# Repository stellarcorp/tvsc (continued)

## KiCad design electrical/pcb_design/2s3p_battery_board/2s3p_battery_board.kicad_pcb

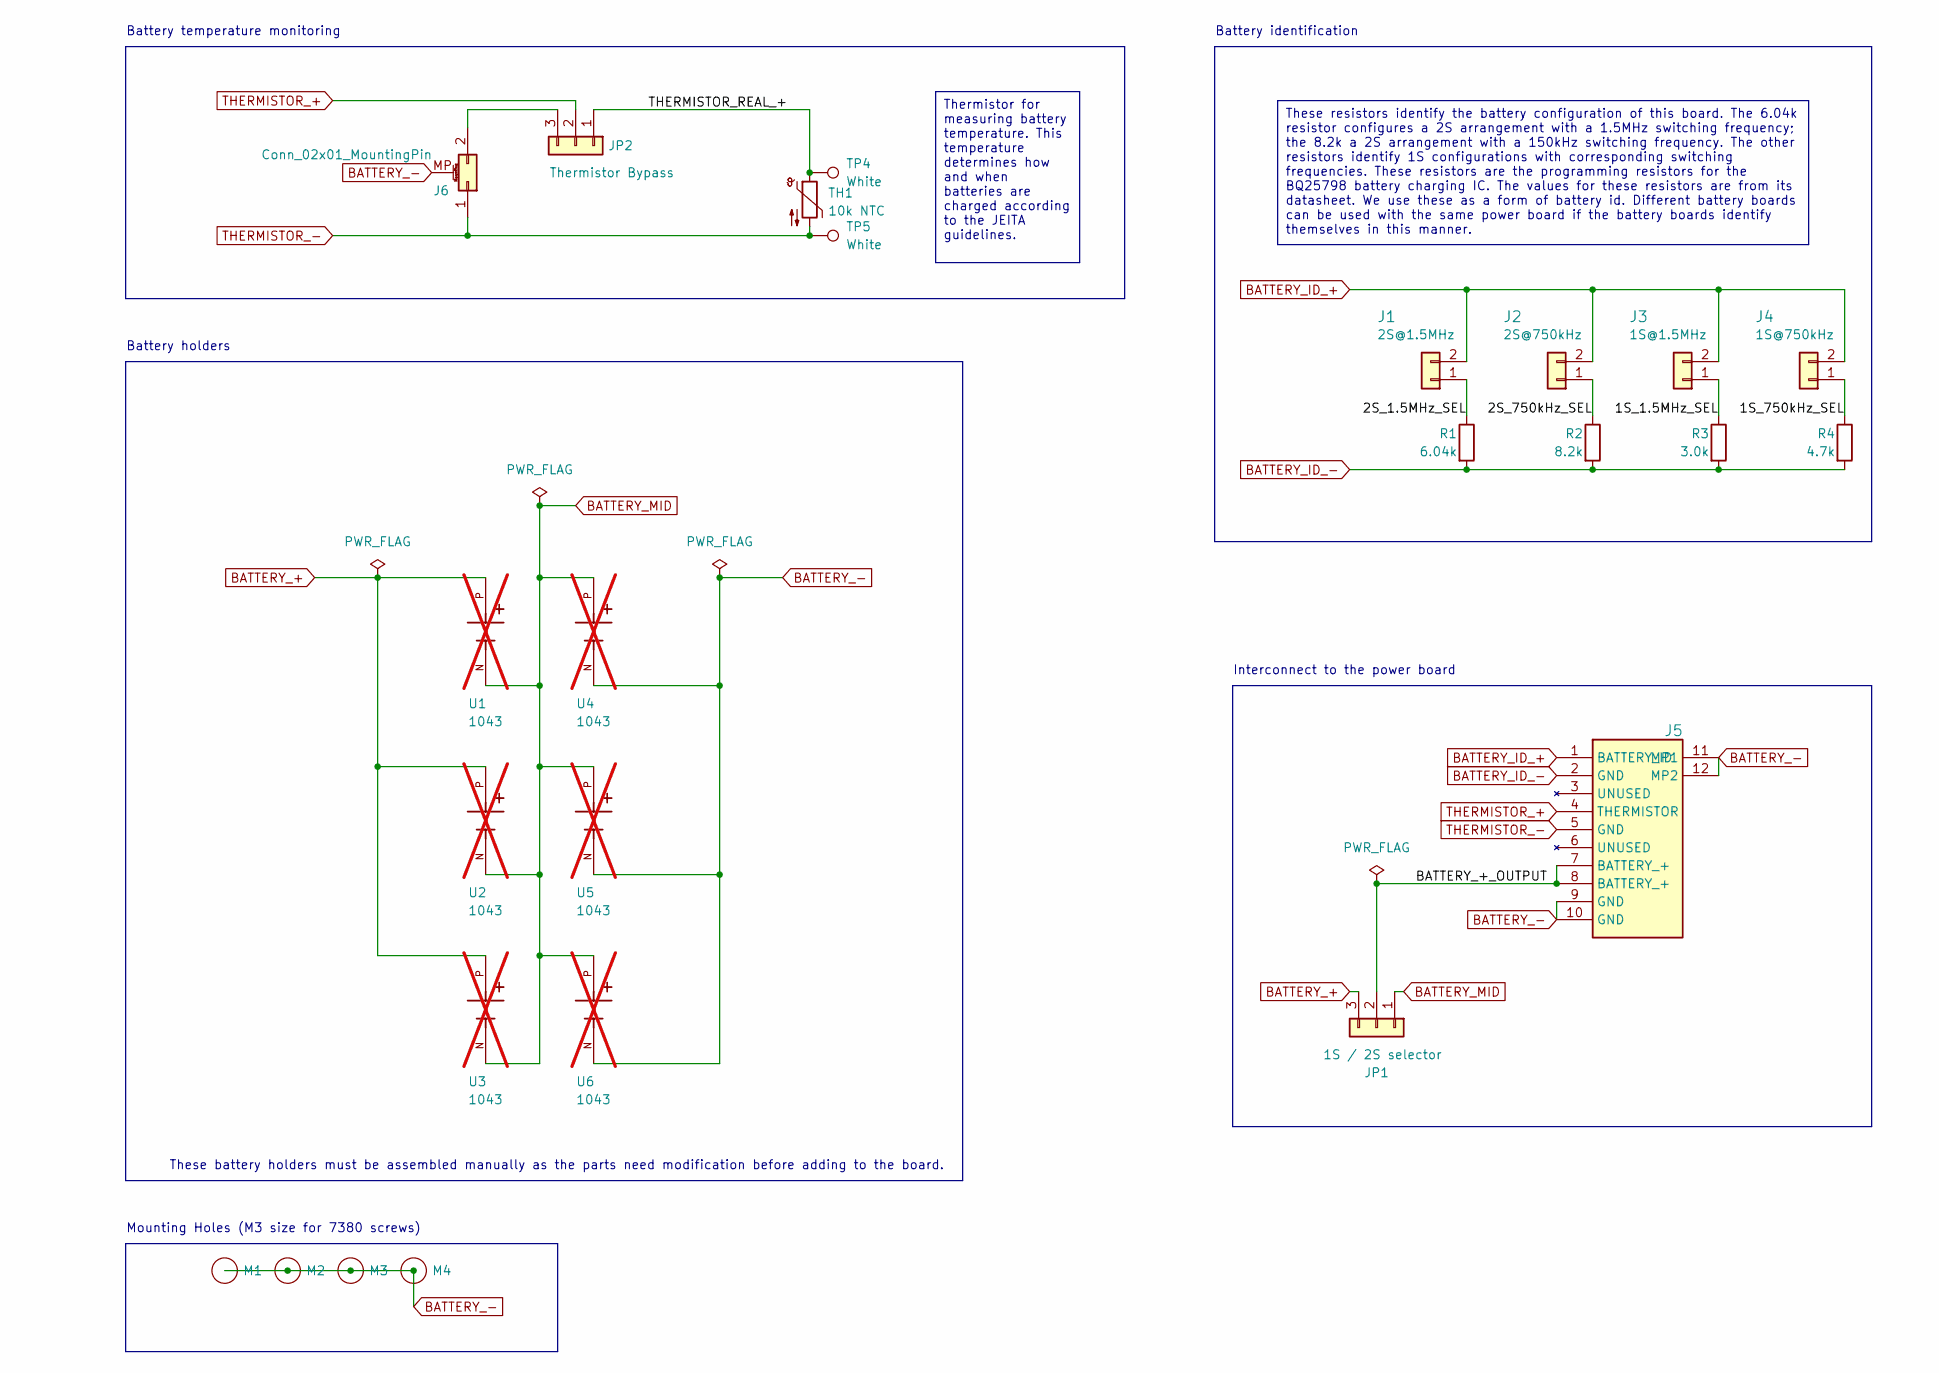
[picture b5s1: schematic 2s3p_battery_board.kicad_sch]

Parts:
J1, J2, J3, J4: 2-pin Header; PinHeader_1x02_P1.27mm_Vertical; Manufacturer Part Number X1321WV-2x01J-C30D23
J5: Interconnect_Battery_Power-Battery_side; 504050-1091; MPN C5375652
J6: Conn_02x01_MountingPin; Molex_Pico-Clasp_501331-0207_1x02-1MP_P1.00mm_Vertical; MPN C587859
JP1, JP2: Conn_01x03; HDRV3W64P0X254_1X3_762X254X869P; MPN C2915006; Mouser Part Number 710-61300311121
M1, M2, M3, M4: MountingHole_3.2mm_M3_ISO7380_Pad_TopBottom
R1: 6.04k; R_0603_1608Metric; MPN C114631
R2: 8.2k; R_0603_1608Metric; MPN C114637
R3: 3.0k; R_0603_1608Metric; MPN C126358
R4: 4.7k; R_0603_1608Metric; MPN C99782
TH1: 10k NTC; R_0402_1005Metric; MPN C336815
TP4, TP5: White; Keystone_5002; MPN C238123
U1, U2, U3, U4, U5, U6: 1043; BAT_1043; Manufacturer Part Number 1043; not fitted

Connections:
/1S_1.5MHz_SEL: J3.1, R3.1
/1S_750kHz_SEL: J4.1, R4.1
/2S_1.5MHz_SEL: J1.1, R1.1
/2S_750kHz_SEL: J2.1, R2.1
/BATTERY_+_OUTPUT: J5.7 (BATTERY_+), J5.8 (BATTERY_+), JP1.2
/THERMISTOR_REAL_+: JP2.1, TH1.1, TP4.1
BATTERY_+: JP1.3, U1.P, U2.P, U3.P
BATTERY_-: J5.9 (GND), J5.10 (GND), J5.11 (MP1), J5.12 (MP2), J6.MP (MountPin), M1.1 (Hole), M2.1 (Hole), M3.1 (Hole), M4.1 (Hole), U4.N, U5.N, U6.N
BATTERY_ID_+: J1.2, J2.2, J3.2, J4.2, J5.1 (BATTERY_ID)
BATTERY_ID_-: J5.2 (GND), R1.2, R2.2, R3.2, R4.2
BATTERY_MID: JP1.1, U1.N, U2.N, U3.N, U4.P, U5.P, U6.P
unnamed: J6.2, JP2.3
THERMISTOR_+: J5.4 (THERMISTOR), JP2.2
THERMISTOR_-: J5.5 (GND), J6.1, TH1.2, TP5.1

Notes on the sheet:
Thermistor for measuring battery temperature. This temperature determines how and when batteries are charged according to the JEITA guidelines.
These resistors identify the battery configuration of this board. The 6.04k resistor configures a 2S arrangement with a 1.5MHz switching frequency; the 8.2k a 2S arrangement with a 150kHz switching frequency. The other resistors identify 1S configurations with corresponding switching frequencies. T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
Mounting Holes (M3 size for 7380 screws)
Battery identification
Battery temperature monitoring
Battery holders
These battery holders must be assembled manually as the parts need modification before adding to the board.
Interconnect to the power board

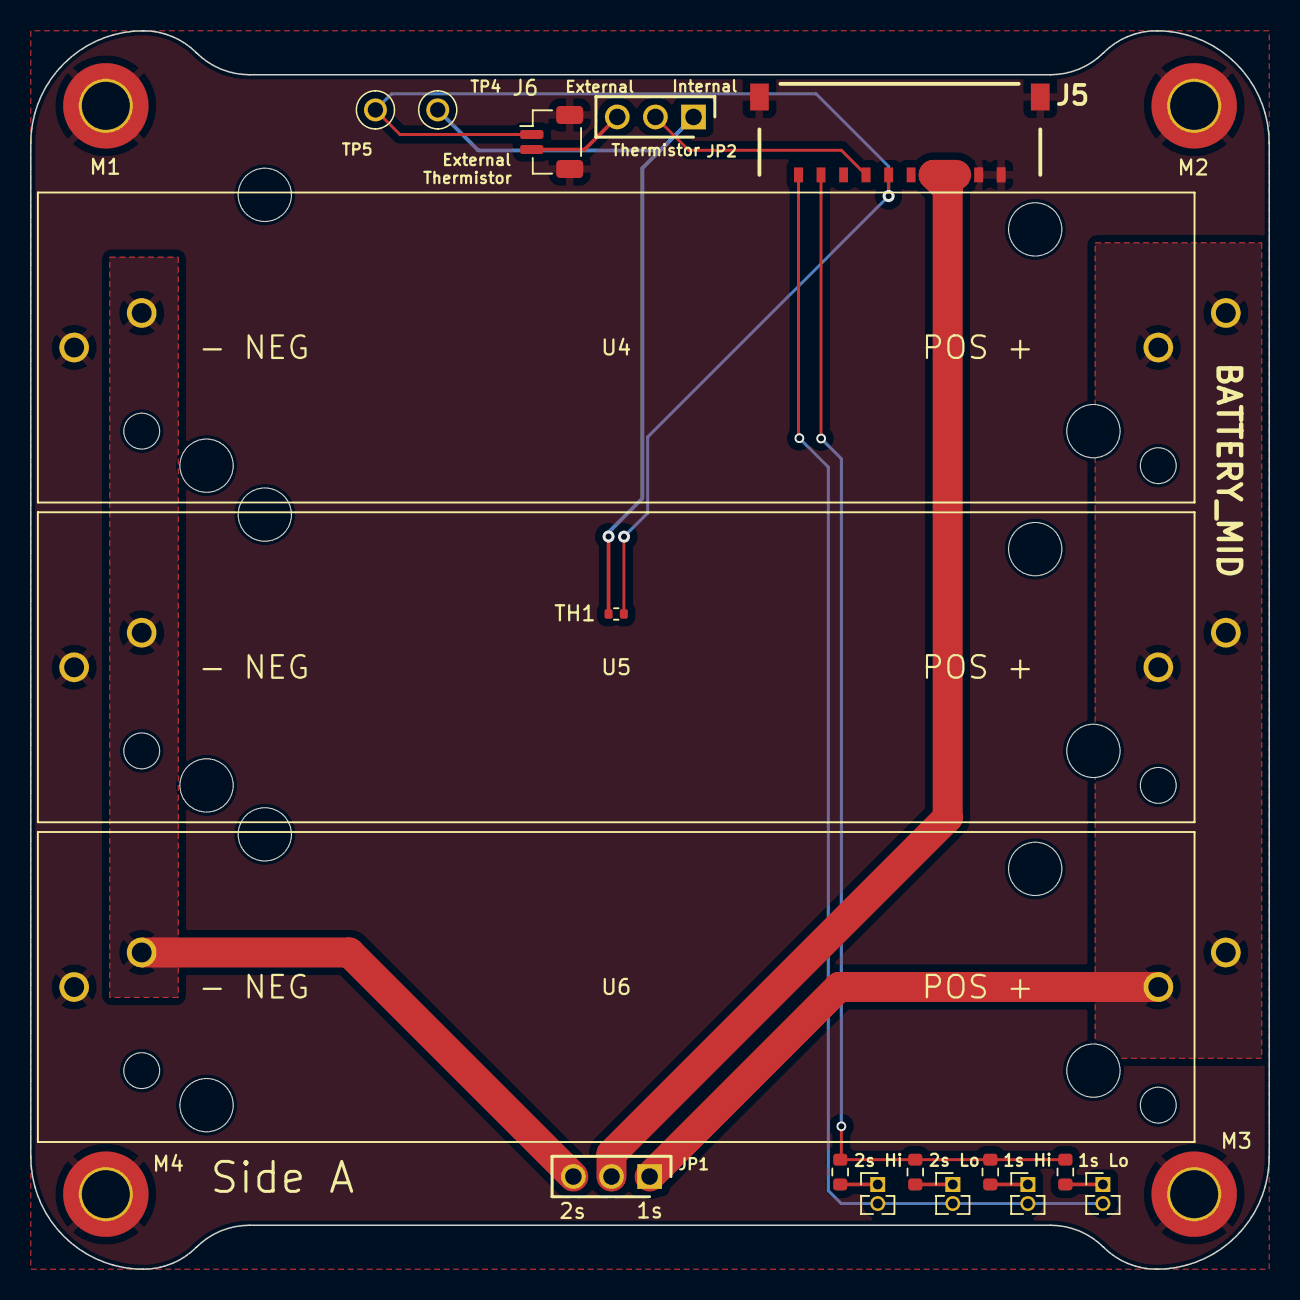
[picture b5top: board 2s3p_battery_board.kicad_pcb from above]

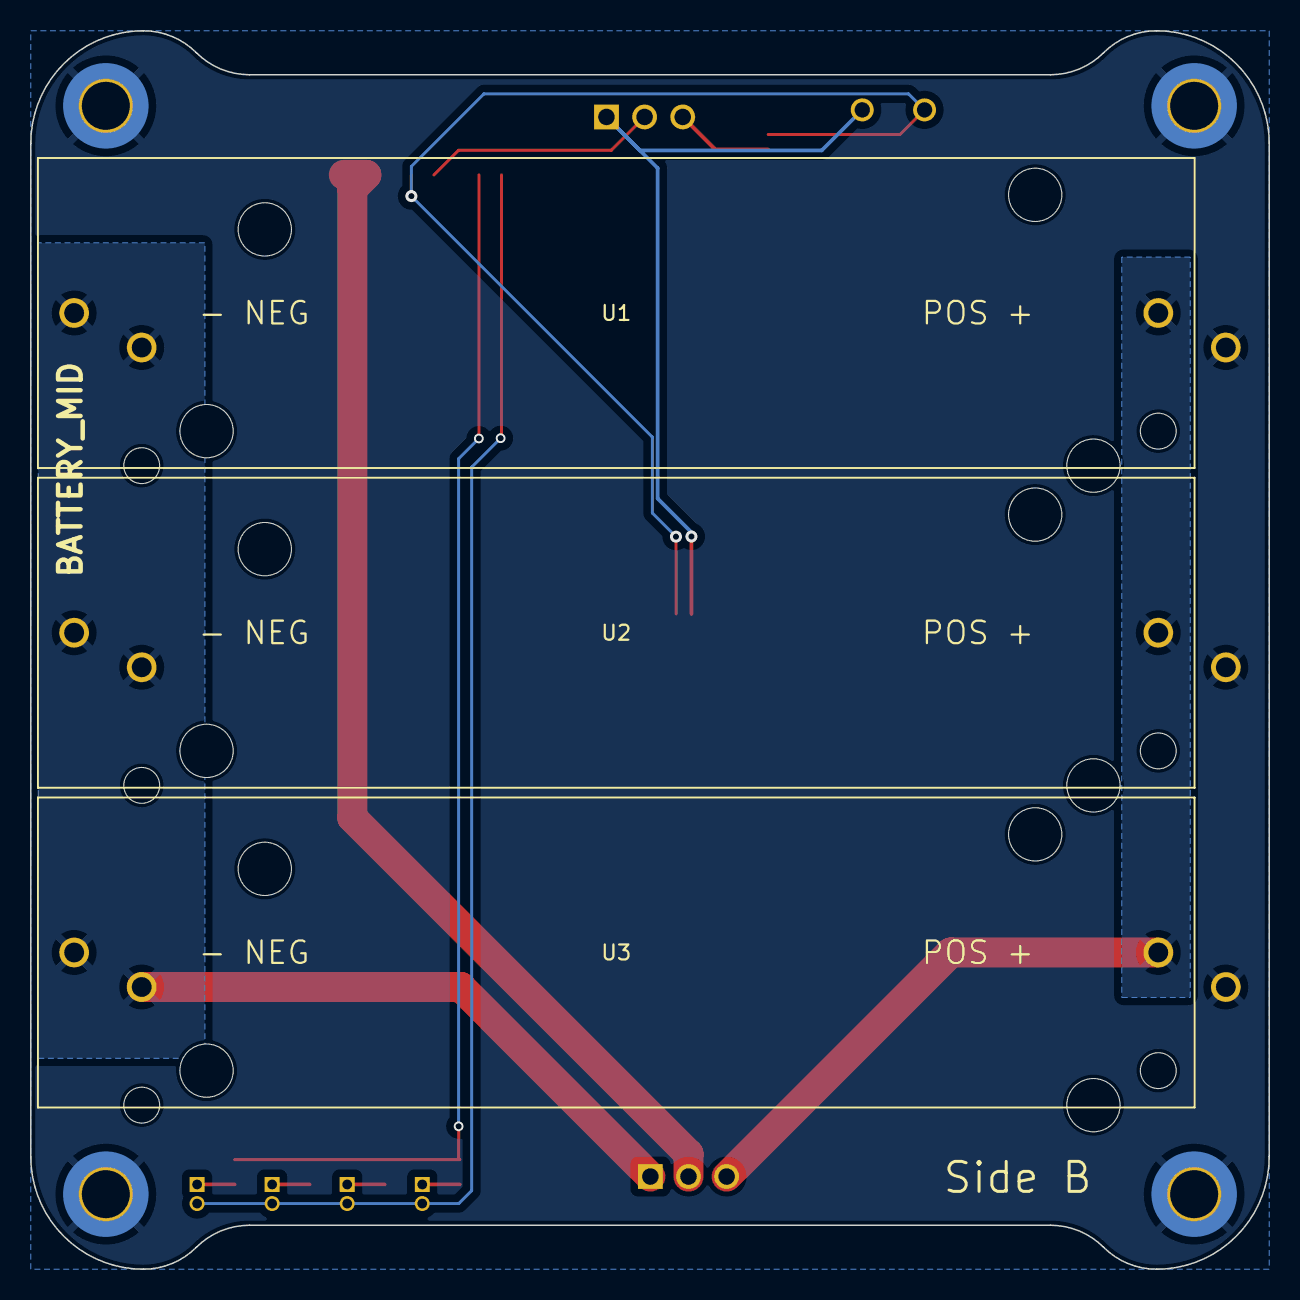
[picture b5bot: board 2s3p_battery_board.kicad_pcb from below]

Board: 2 copper layers, 82.5 x 82.5 mm, 25 parts (3 on the bottom side), 14 nets.

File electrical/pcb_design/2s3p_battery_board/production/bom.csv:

Designator,Footprint,Quantity,Value,LCSC Part #
"J1, J2, J3, J4",PinHeader_1x02_P1.27mm_Vertical,4,2-pin Header,C2881948
J5,504050-1091,1,Interconnect_Battery_Power-Battery_side,C5375652
J6,Molex_Pico-Clasp_501331-0207_1x02-1MP_P1.00mm_Vertical,1,Conn_02x01_MountingPin,C587859
"JP1, JP2",HDRV3W64P0X254_1X3_762X254X869P,2,Conn_01x03,C2915006
R1,0603,1,6.04k,C114631
R2,0603,1,8.2k,C114637
R3,0603,1,3.0k,C126358
R4,0603,1,4.7k,C99782
TH1,0402,1,10k NTC,C336815
"TP4, TP5",Keystone_5002,2,White,C238123

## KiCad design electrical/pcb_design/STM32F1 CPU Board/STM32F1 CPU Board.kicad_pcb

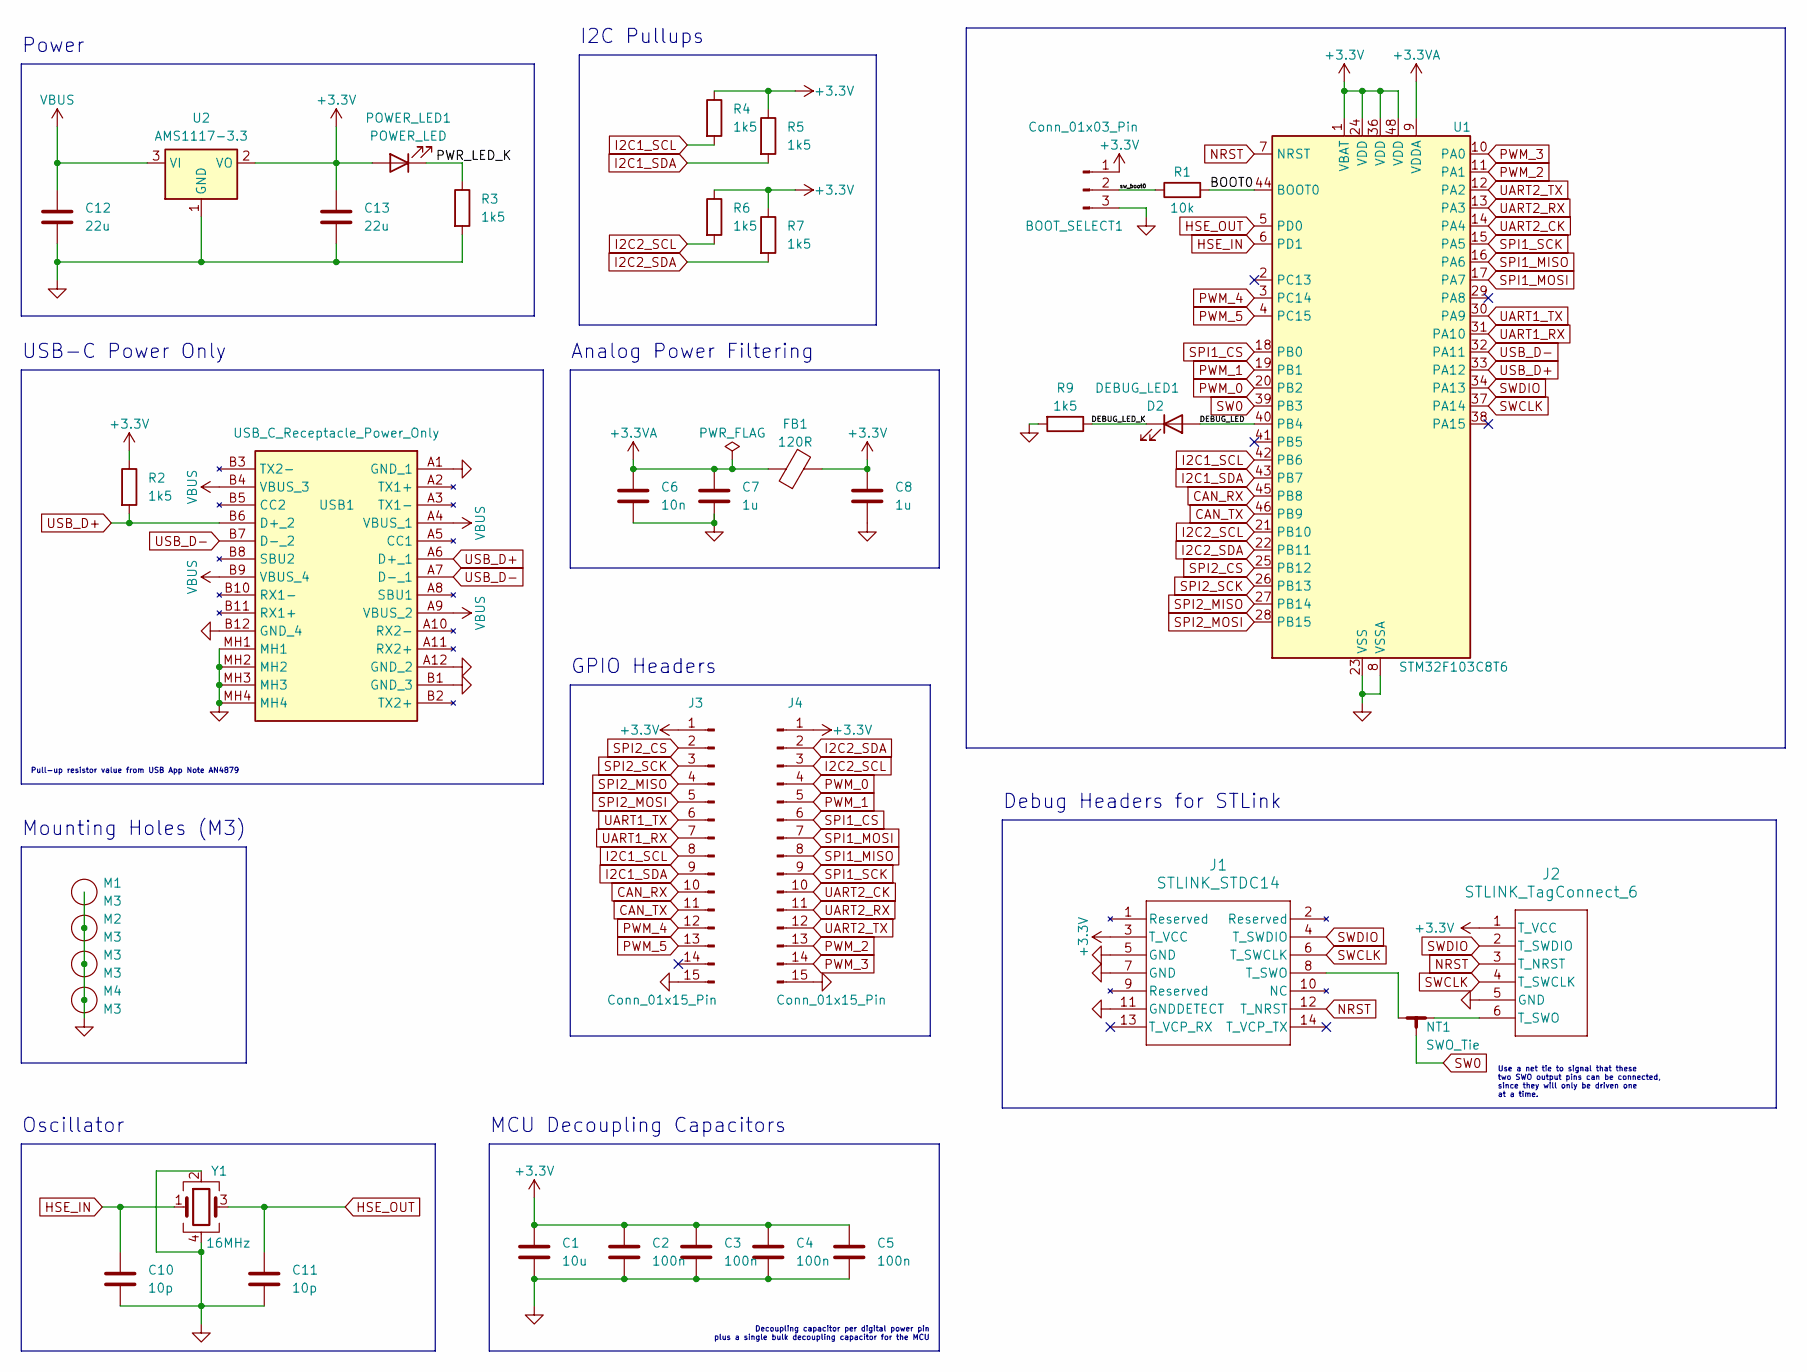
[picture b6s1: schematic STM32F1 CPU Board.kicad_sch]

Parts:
BOOT_SELECT1: Conn_01x03_Pin; PinHeader_1x03_P2.54mm_Vertical
C1: 10u; C_0603_1608Metric; MPN C19702
C2, C3, C4, C5: 100n; C_0402_1005Metric; MPN C1525
C6: 10n; C_0402_1005Metric; MPN C15195
C7, C8: 1u; C_0603_1608Metric; MPN C15849
C10, C11: 10p; C_0402_1005Metric; MPN C32949
C12, C13: 22u; C_0805_2012Metric; MPN C45783
D2: DEBUG_LED1; LED_0603_1608Metric; MPN C72041
FB1: 120R; L_0603_1608Metric; MPN C22787
J1: STLINK_STDC14; PinHeader_2x07_P1.27mm_Vertical; MPN C2881789
J2: STLINK_TagConnect_6; Tag-Connect_TC2030-IDC-NL_2x03_P1.27mm_Vertical
J3, J4: Conn_01x15_Pin; PinSocket_1x15_P2.54mm_Vertical; MPN C2883481
M1, M2, M3, M4: M3; MountingHole_3.2mm_M3_ISO7380_Pad_TopBottom
NT1: SWO_Tie; NetTie-3_SMD_Pad0.5mm
POWER_LED1: POWER_LED; LED_0603_1608Metric; MPN C72043
R1: 10k; R_0402_1005Metric; MPN C25744
R2, R3, R4, R5, R6, R7, R9: 1k5; R_0402_1005Metric; MPN C25867
U1: STM32F103C8T6; LQFP-48_7x7mm_P0.5mm; MPN C8734
U2: AMS1117-3.3; SOT-223-3_TabPin2; MPN C6186
USB1: USB_C_Receptacle_Power_Only; 12401832E402A; MPN C464604
Y1: 16MHz; Crystal_SMD_3225-4Pin_3.2x2.5mm; MPN C2857621

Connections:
+3.3V: BOOT_SELECT1.1, C1.1, C2.1, C3.1, C4.1, C5.1, C8.1, C13.1, FB1.2, J1.3 (T_VCC), J2.1 (T_VCC), J3.1, J4.1, POWER_LED1.2 (A), R2.1, R4.1, R5.1, R6.1, R7.1, U1.1 (VBAT), U1.24 (VDD), U1.36 (VDD), U1.48 (VDD), U2.2 (VO)
+3.3VA: C6.1, C7.1, FB1.1, U1.9 (VDDA)
/BOOT0: R1.2, U1.44 (BOOT0)
/DEBUG_LED: D2.2 (A), U1.40 (PB4)
/DEBUG_LED_K: D2.1 (K), R9.1
/PWR_LED_K: POWER_LED1.1 (K), R3.1
/sw_boot0: BOOT_SELECT1.2, R1.1
CAN_RX: J3.10, U1.45 (PB8)
CAN_TX: J3.11, U1.46 (PB9)
GND: BOOT_SELECT1.3, C1.2, C2.2, C3.2, C4.2, C5.2, C6.2, C7.2, C8.2, C10.2, C11.2, C12.2, C13.2, J1.5 (GND), J1.7 (GND), J1.11 (GNDDETECT), J2.5 (GND), J3.15, J4.15, M1.1 (Hole), M2.1 (Hole), M3.1 (Hole), M4.1 (Hole), R3.2, R9.2, U1.8 (VSSA), U1.23 (VSS), U1.35 (VSS), U1.47 (VSS), U2.1 (GND), USB1.A1 (GND_1), USB1.A12 (GND_2), USB1.B1 (GND_3), USB1.B12 (GND_4), USB1.MH1, USB1.MH2, USB1.MH3, USB1.MH4, Y1.2, Y1.4
HSE_IN: C10.1, U1.6 (PD1), Y1.1
HSE_OUT: C11.1, U1.5 (PD0), Y1.3
I2C1_SCL: J3.8, R4.2, U1.42 (PB6)
I2C1_SDA: J3.9, R5.2, U1.43 (PB7)
I2C2_SCL: J4.3, R6.2, U1.21 (PB10)
I2C2_SDA: J4.2, R7.2, U1.22 (PB11)
NRST: J1.12 (T_NRST), J2.3 (T_NRST), U1.7 (NRST)
unnamed: J1.8 (T_SWO), NT1.1
unnamed: J2.6 (T_SWO), NT1.2
PWM_0: J4.4, U1.20 (PB2)
PWM_1: J4.5, U1.19 (PB1)
PWM_2: J4.13, U1.11 (PA1)
PWM_3: J4.14, U1.10 (PA0)
PWM_4: J3.12, U1.3 (PC14)
PWM_5: J3.13, U1.4 (PC15)
SPI1_CS: J4.6, U1.18 (PB0)
SPI1_MISO: J4.8, U1.16 (PA6)
SPI1_MOSI: J4.7, U1.17 (PA7)
SPI1_SCK: J4.9, U1.15 (PA5)
SPI2_CS: J3.2, U1.25 (PB12)
SPI2_MISO: J3.4, U1.27 (PB14)
SPI2_MOSI: J3.5, U1.28 (PB15)
SPI2_SCK: J3.3, U1.26 (PB13)
SW0: NT1.3, U1.39 (PB3)
SWCLK: J1.6 (T_SWCLK), J2.4 (T_SWCLK), U1.37 (PA14)
SWDIO: J1.4 (T_SWDIO), J2.2 (T_SWDIO), U1.34 (PA13)
UART1_RX: J3.7, U1.31 (PA10)
UART1_TX: J3.6, U1.30 (PA9)
UART2_CK: J4.10, U1.14 (PA4)
UART2_RX: J4.11, U1.13 (PA3)
UART2_TX: J4.12, U1.12 (PA2)
USB_D+: R2.2, U1.33 (PA12), USB1.A6 (D+_1), USB1.B6 (D+_2)
USB_D-: U1.32 (PA11), USB1.A7 (D-_1), USB1.B7 (D-_2)
VBUS: C12.1, U2.3 (VI), USB1.A4 (VBUS_1), USB1.A9 (VBUS_2), USB1.B4 (VBUS_3), USB1.B9 (VBUS_4)

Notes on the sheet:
Use a net tie to signal that these two SWO output pins can be connected, since they will only be driven one at a time.
GPIO Headers
Decoupling capacitor per digital power pin plus a single bulk decoupling capacitor for the MCU
I2C Pullups
Mounting Holes (M3)
Debug Headers for STLink
Power
Pull-up resistor value from USB App Note AN4879
MCU Decoupling Capacitors
Analog Power Filtering
Oscillator
USB-C Power Only

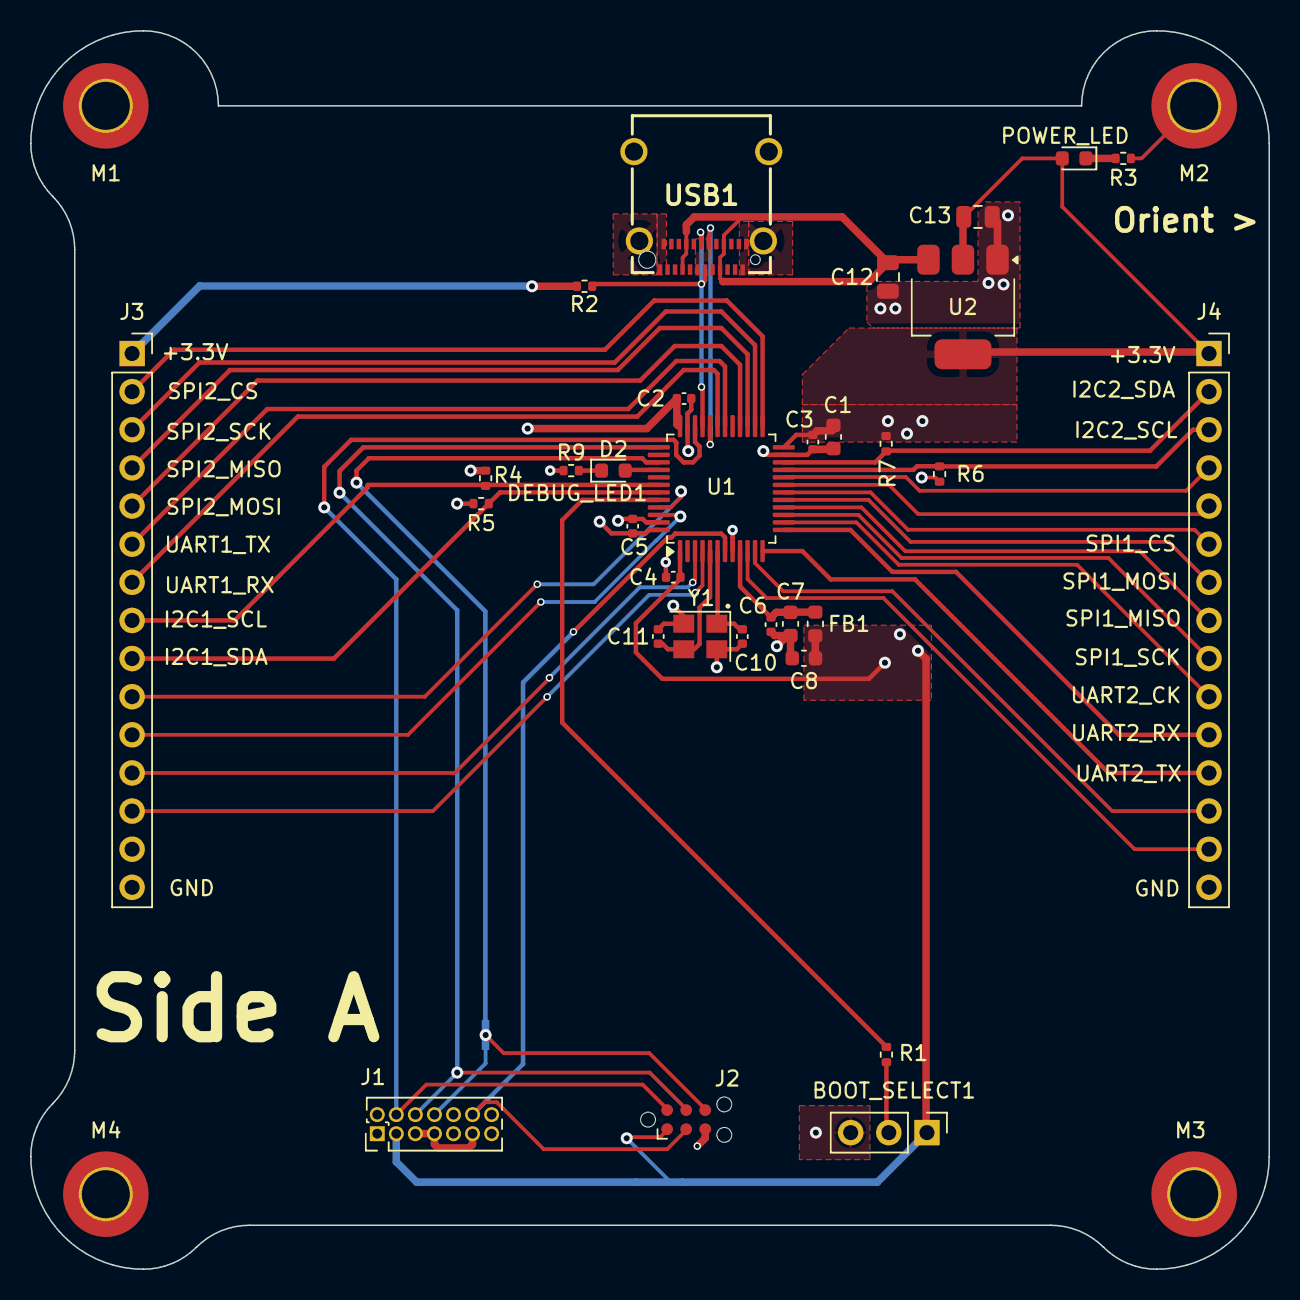
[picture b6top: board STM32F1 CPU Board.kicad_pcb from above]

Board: 2 copper layers, 82.5 x 82.5 mm, 37 parts (1 on the bottom side), 44 nets.

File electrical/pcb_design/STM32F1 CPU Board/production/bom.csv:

Designator,Footprint,Quantity,Value,LCSC Part #
C1,0603,1,10u,C19702
"C10, C11",0402,2,10p,C32949
"C12, C13",0805,2,22u,C45783
"C2, C3, C4, C5",0402,4,100n,C1525
C6,0402,1,10n,C15195
"C7, C8",0603,2,1u,C15849
D2,0603,1,DEBUG_LED1,C72041
FB1,0603,1,120R,C22787
J1,PinHeader_2x07_P1.27mm_Vertical,1,STLINK_STDC14,C2881789
"J3, J4",PinSocket_1x15_P2.54mm_Vertical,2,Conn_01x15_Pin,C2883481
POWER_LED1,0603,1,POWER_LED,C72043
R1,0402,1,10k,C25744
"R2, R3, R4, R5, R6, R7, R9",0402,7,1k5,C25867
U1,LQFP-48_7x7mm_P0.5mm,1,STM32F103C8T6,C8734
U2,SOT-223-3_TabPin2,1,AMS1117-3.3,C6186
USB1,12401832E402A,1,USB_C_Receptacle_Power_Only,C464604
Y1,Crystal_SMD_3225-4Pin_3.2x2.5mm,1,16MHz,C2857621
